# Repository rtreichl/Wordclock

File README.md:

# WortUhr

Wortuhr mit 12 × 12 Buchstaben, 500 × 500 mm. Frontplatte aus 1 mm Cortenstahl, die von Magneten gehalten wird. Lichtgitter aus 4 gedruckten Teilen. Vier gleiche LED-Platinen mit SK6812 RGBW; eine davon trägt als Master USB-C Power Delivery und den ESP32-S3 (ESPHome oder WLED). Aufbauhöhe 36 mm.

| Ordner | Inhalt |
|---|---|
| `00_Design/` | Grafik und Buchstabenlayout: Affinity-Datei, Pattern-SVGs, Frontplatten-DXF/-SVG (Schrift Sencilla) |
| `01_Mechanic/` | FreeCAD-Hauptmodell `FrontPlatte-Bestellung.FCStd` und Fertigungsdateien |
| `01_Mechanic/Frontplatte/` | Frontplatte 1 mm (STEP), DXF mit Lichtleiter-Bohrung zum Bestellen |
| `01_Mechanic/Gitter/` | Lichtgitter Q1–Q4 (STEP und druckfertige 3MF) |
| `01_Mechanic/Rueckrahmen/` | 8 Rückrahmen-Leisten (STEP) und 2 Druckplatten (3MF, je ≤ 254 × 254 mm) |
| `01_Mechanic/Diffusor/` | Diffusor 30 × 30 × 2 mm (DXF/STEP), 144 Stück |
| `02_Electronics/KiCad/` | KiCad-Projekt, Generator-Skripte (`tools/`), Projektbibliotheken und Platzhalter-3D-Modelle |
| `02_Electronics/BESTUECKUNG.md` | Bestückung, Kantenbrücken, Montage, WLED-Einstellungen |
| `02_Electronics/KiCad/ROUTING_GUIDE.md` | Regeln mit ID für Schaltplan, Layout, Routing und Review |
| `03_Software/ESPHome/` | Firmware für den ESP32-S3 (Uhrzeit per NTP, Home Assistant, Weboberfläche), siehe `README.md` dort |
| `03_Software/WLED/` | LED-Maps für WLED (1 oder 2 LEDs je Kammer) |
| `04_Rendering/` | Blender-Skript, Szene, Netze und Renderbilder |
| `05_Production/` | Geprüfte Fertigungsdaten je Bauteil mit Bericht `QUALIFIKATION.md`; Prüfskripte in `tools/` |
| `06_Datenblätter/` | Datenblätter, nur lokal (nicht eingecheckt) |
| `99_Archive/` | Ältere Modelle, Zwischenstände und erledigte Einmal-Skripte |

Ein Bild mit neuen Einstellungen rendern:

```
blender.exe -b -P 04_Rendering/render_wortuhr.py -- --samples 256 --res 2000x2000 --view angle
```

## Arbeiten am Projekt

Schaltplan und Platine entstehen aus `02_Electronics/KiCad/tools/design.py`. Jede Änderung wird gegen die Grenzen des Fertigers und gegen die Projektregeln geprüft; der GitHub-Workflow `production.yml` führt alle Prüfungen bei jedem Push aus. Regeln, Abläufe und Befehle stehen in `CLAUDE.md`, die Prüfskripte beschreibt `05_Production/tools/README.md`.

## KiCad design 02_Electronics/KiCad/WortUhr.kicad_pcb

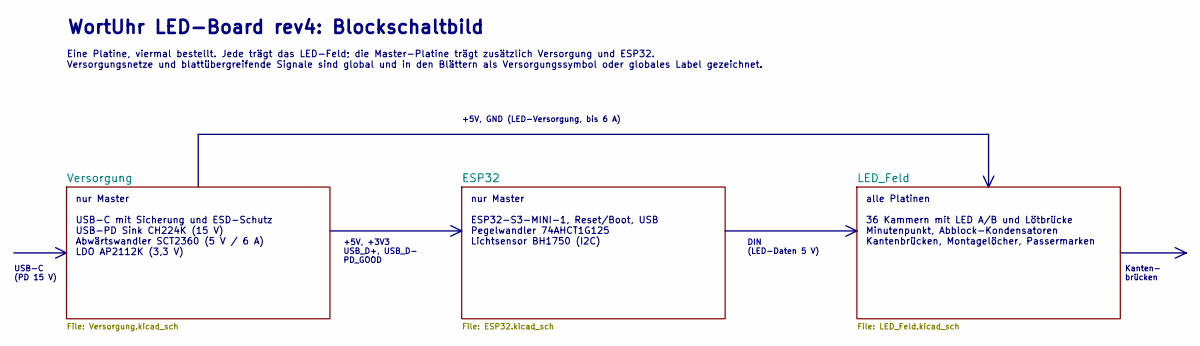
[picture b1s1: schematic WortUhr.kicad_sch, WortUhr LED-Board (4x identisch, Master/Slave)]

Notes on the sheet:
WortUhr LED-Board rev4: Blockschaltbild
Eine Platine, viermal bestellt. Jede trägt das LED-Feld; die Master-Platine trägt zusätzlich Versorgung und ESP32. Versorgungsnetze und blattübergreifende Signale sind global und in den Blättern als Versorgungssymbol oder globales Label gezeichnet.
nur Master USB-C mit Sicherung und ESD-Schutz USB-PD Sink CH224K (15 V) Abwärtswandler SCT2360 (5 V / 6 A) LDO AP2112K (3,3 V)
nur Master ESP32-S3-MINI-1, Reset/Boot, USB Pegelwandler 74AHCT1G125 Lichtsensor BH1750 (I2C)
alle Platinen 36 Kammern mit LED A/B und Lötbrücke Minutenpunkt, Abblock-Kondensatoren Kantenbrücken, Montagelöcher, Passermarken
+5V, +3V3 USB_D+, USB_D- PD_GOOD
DIN (LED-Daten 5 V)
+5V, GND (LED-Versorgung, bis 6 A)
USB-C (PD 15 V)
Kanten- brücken

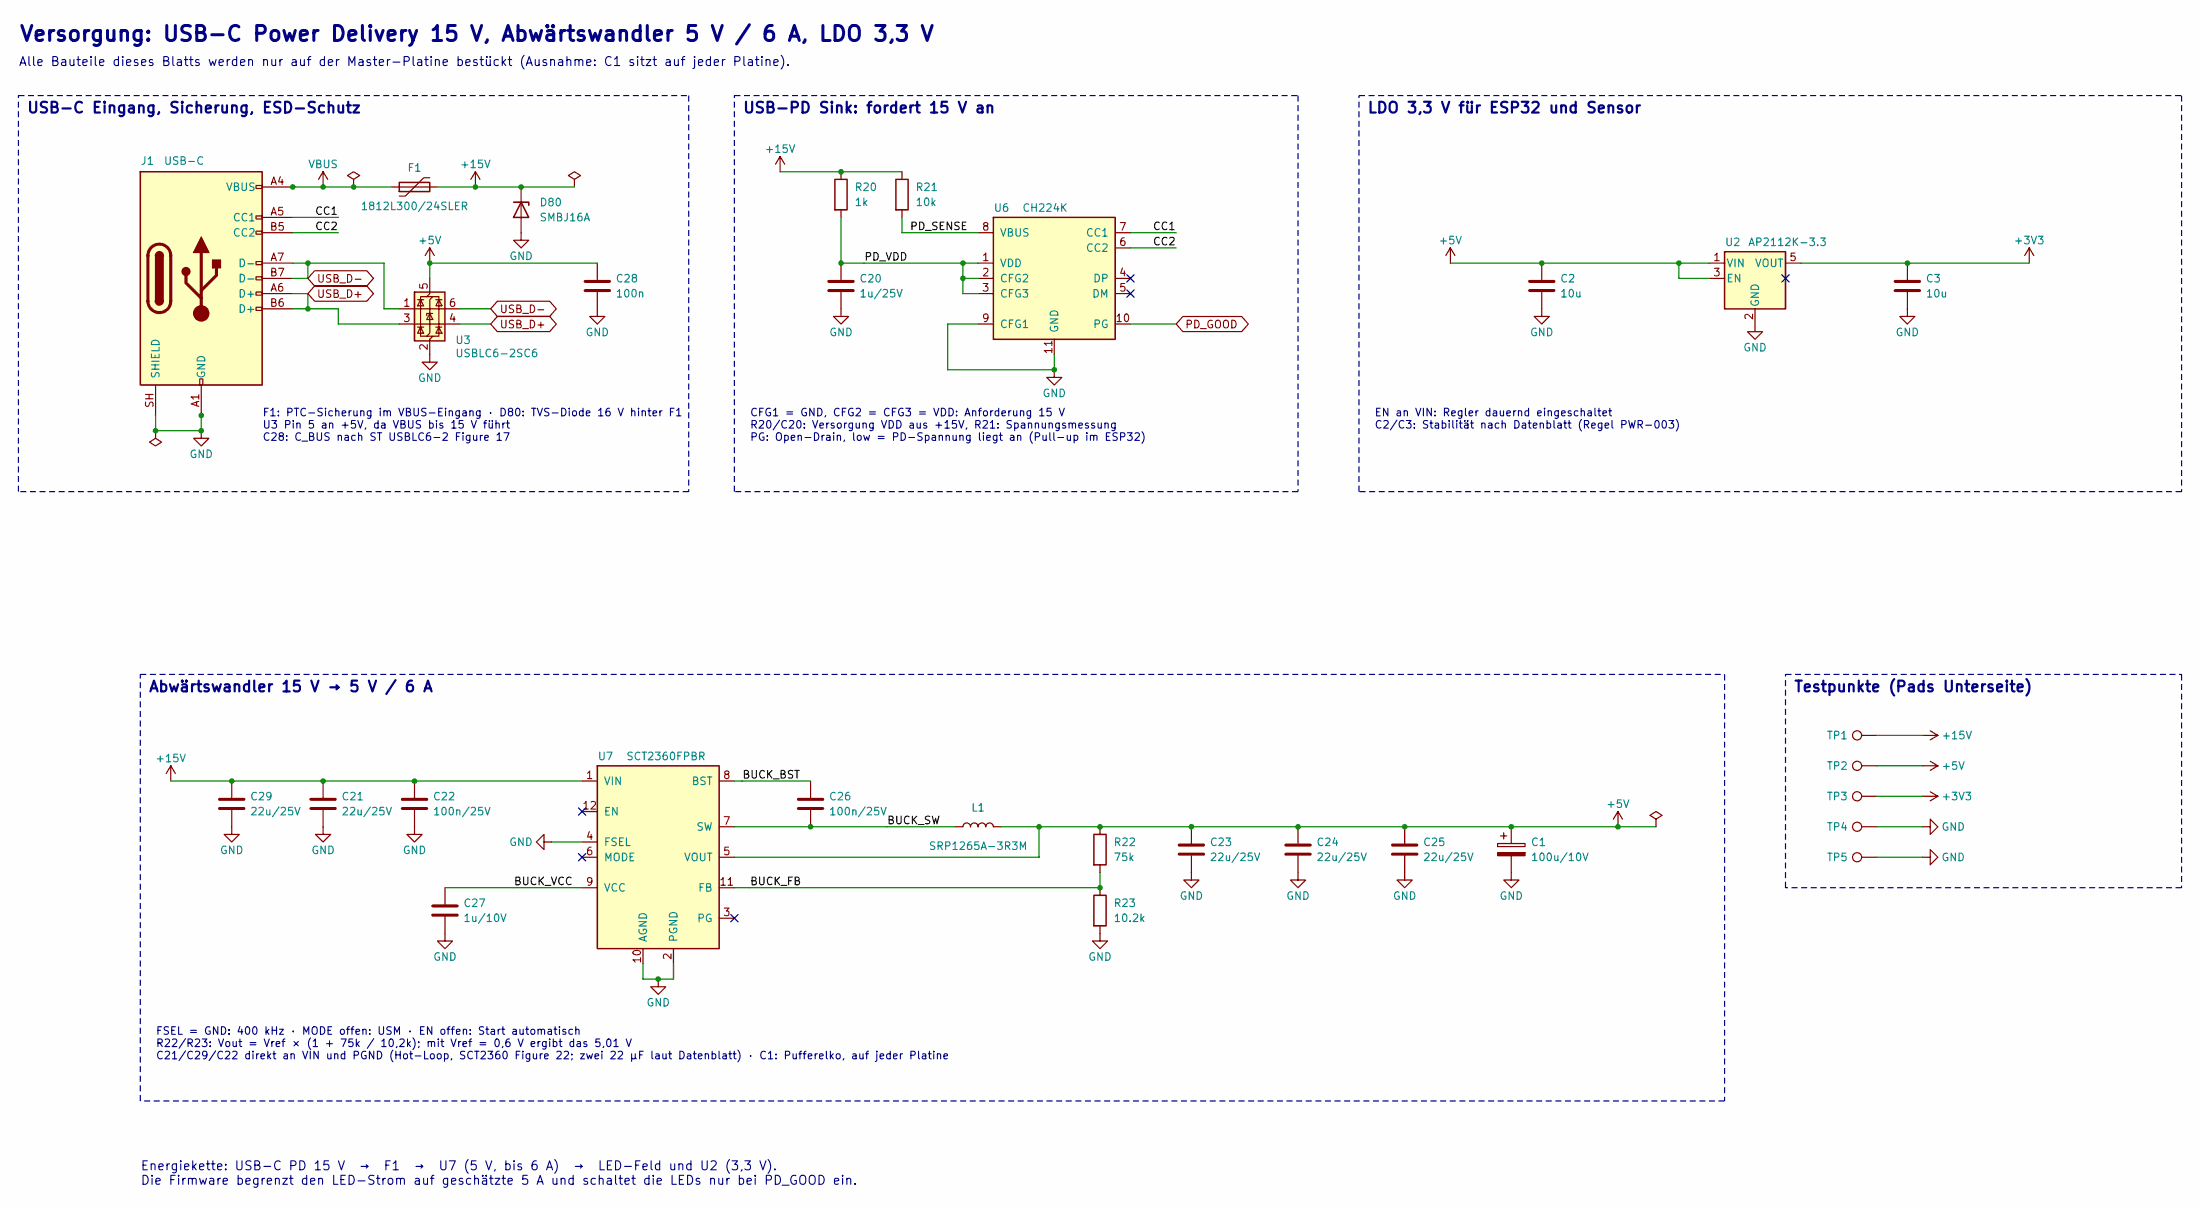
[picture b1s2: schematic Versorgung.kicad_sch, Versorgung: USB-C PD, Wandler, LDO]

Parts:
C1: 100u/10V; CP_Elec_6.3x7.7; MPN UWT1A101MCL1GB; DigiKey 493-2165-1-ND
C2, C3: 10u; C_0805_2012Metric; MPN TMK212BBJ106MG-T; DigiKey 587-6025-1-ND
C20: 1u/25V; C_0603_1608Metric; MPN C0603C105K3RACTU; DigiKey 399-C0603C105K3RACTUCT-ND
C21, C23, C24, C25, C29: 22u/25V; C_1206_3216Metric; MPN CC1206MKX5R8BB226; DigiKey 311-3522-1-ND
C22, C26: 100n/25V; C_0603_1608Metric; MPN C0603C104K5RACTU; DigiKey 399-C0603C104K5RACTUCT-ND
C27: 1u/10V; C_0603_1608Metric; MPN C0603C105K3RACTU; DigiKey 399-C0603C105K3RACTUCT-ND
C28: 100n; C_0603_1608Metric; MPN C0603C104K5RACTU; DigiKey 399-C0603C104K5RACTUCT-ND
D80: SMBJ16A; D_SMB; MPN SMBJ16A
F1: 1812L300/24SLER; Fuse_1812_4532Metric; MPN 1812L300/24SLER; DigiKey 18-1812L300/24SLERCT-ND
J1: USB-C; USB_C_Receptacle_HRO_TYPE-C-31-M-12; MPN TYPE-C-31-M-12
L1: SRP1265A-3R3M; L_Bourns_SRP1245A; MPN SRP1265A-3R3M; DigiKey SRP1265A-3R3MCT-ND
R20: 1k; R_1206_3216Metric; MPN RC1206FR-071KL; DigiKey 311-1.00KFRCT-ND
R21: 10k; R_0603_1608Metric; MPN ERJ-3EKF1002V; DigiKey P10.0KHCT-ND
R22: 75k; R_0603_1608Metric; MPN ERJ-3EKF7502V; DigiKey P75.0KHCT-ND
R23: 10.2k; R_0603_1608Metric; MPN ERJ-3EKF1022V; DigiKey P10.2KHCT-ND
TP1: +15V; TestPoint_Pad_D1.5mm
TP2: +5V; TestPoint_Pad_D1.5mm
TP3: +3V3; TestPoint_Pad_D1.5mm
TP4, TP5: GND; TestPoint_Pad_D1.5mm
U2: AP2112K-3.3; SOT-23-5; MPN AP2112K-3.3TRG1; DigiKey AP2112K-3.3TRG1DICT-ND
U3: USBLC6-2SC6; SOT-23-6; MPN USBLC6-2SC6; DigiKey 497-5235-1-ND
U6: CH224K; SSOP-10-1EP_3.9x4.9mm_P1mm_EP2.1x3.3mm; MPN CH224K
U7: SCT2360FPBR; QFN-12_SCT2360; MPN SCT2360FPBR

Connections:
+3V3: C3.1, TP3.1, U2.5 (VOUT); also elsewhere on the board
+5V: C1.1, C2.1, C23.1, C24.1, C25.1, C28.1, L1.2, R22.1, TP2.1, U2.1 (VIN), U2.3 (EN), U3.5 (VBUS), U7.5 (VOUT); also elsewhere on the board
+15V: C21.1, C22.1, C29.1, D80.1 (K), F1.2, R20.1, R21.1, TP1.1, U7.1 (VIN)
/Versorgung/BUCK_BST: C26.1, U7.8 (BST)
/Versorgung/BUCK_FB: R22.2, R23.1, U7.11 (FB)
/Versorgung/BUCK_SW: C26.2, L1.1, U7.7 (SW)
/Versorgung/BUCK_VCC: C27.1, U7.9 (VCC)
/Versorgung/CC1: J1.A5 (CC1), U6.7 (CC1)
/Versorgung/CC2: J1.B5 (CC2), U6.6 (CC2)
/Versorgung/PD_SENSE: R21.2, U6.8 (VBUS)
/Versorgung/PD_VDD: C20.1, R20.2, U6.1 (VDD), U6.2 (CFG2), U6.3 (CFG3)
GND: C1.2, C2.2, C3.2, C20.2, C21.2, C22.2, C23.2, C24.2, C25.2, C27.2, C28.2, C29.2, D80.2 (A), J1.A1 (GND), J1.A12 (GND), J1.B1 (GND), J1.B12 (GND), J1.SH (SHIELD), R23.2, TP4.1, TP5.1, U2.2 (GND), U3.2 (GND), U6.9 (CFG1), U6.11 (GND), U7.2 (PGND), U7.4 (FSEL), U7.10 (AGND); also elsewhere on the board
PD_GOOD: U6.10 (PG); also elsewhere on the board
USB_D+: J1.A6 (D+), J1.B6 (D+), U3.3 (I/O2), U3.4 (I/O2); also elsewhere on the board
USB_D-: J1.A7 (D-), J1.B7 (D-), U3.1 (I/O1), U3.6 (I/O1); also elsewhere on the board
VBUS: F1.1, J1.A4 (VBUS), J1.A9 (VBUS), J1.B4 (VBUS), J1.B9 (VBUS)

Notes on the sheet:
Versorgung: USB-C Power Delivery 15 V, Abwärtswandler 5 V / 6 A, LDO 3,3 V
Alle Bauteile dieses Blatts werden nur auf der Master-Platine bestückt (Ausnahme: C1 sitzt auf jeder Platine).
USB-C Eingang, Sicherung, ESD-Schutz
F1: PTC-Sicherung im VBUS-Eingang · D80: TVS-Diode 16 V hinter F1 U3 Pin 5 an +5V, da VBUS bis 15 V führt C28: C_BUS nach ST USBLC6-2 Figure 17
USB-PD Sink: fordert 15 V an
CFG1 = GND, CFG2 = CFG3 = VDD: Anforderung 15 V R20/C20: Versorgung VDD aus +15V, R21: Spannungsmessung PG: Open-Drain, low = PD-Spannung liegt an (Pull-up im ESP32)
LDO 3,3 V für ESP32 und Sensor
EN an VIN: Regler dauernd eingeschaltet C2/C3: Stabilität nach Datenblatt (Regel PWR-003)
Abwärtswandler 15 V → 5 V / 6 A
FSEL = GND: 400 kHz · MODE offen: USM · EN offen: Start automatisch R22/R23: Vout = Vref × (1 + 75k / 10,2k); mit Vref = 0,6 V ergibt das 5,01 V C21/C29/C22 direkt an VIN und PGND (Hot-Loop, SCT2360 Figure 22; zwei 22 µF laut Datenblatt) · C1: Pufferelko, auf jeder Platine
Testpunkte (Pads Unterseite)
Energiekette: USB-C PD 15 V → F1 → U7 (5 V, bis 6 A) → LED-Feld und U2 (3,3 V). Die Firmware begrenzt den LED-Strom auf geschätzte 5 A und schaltet die LEDs nur bei PD_GOOD ein.

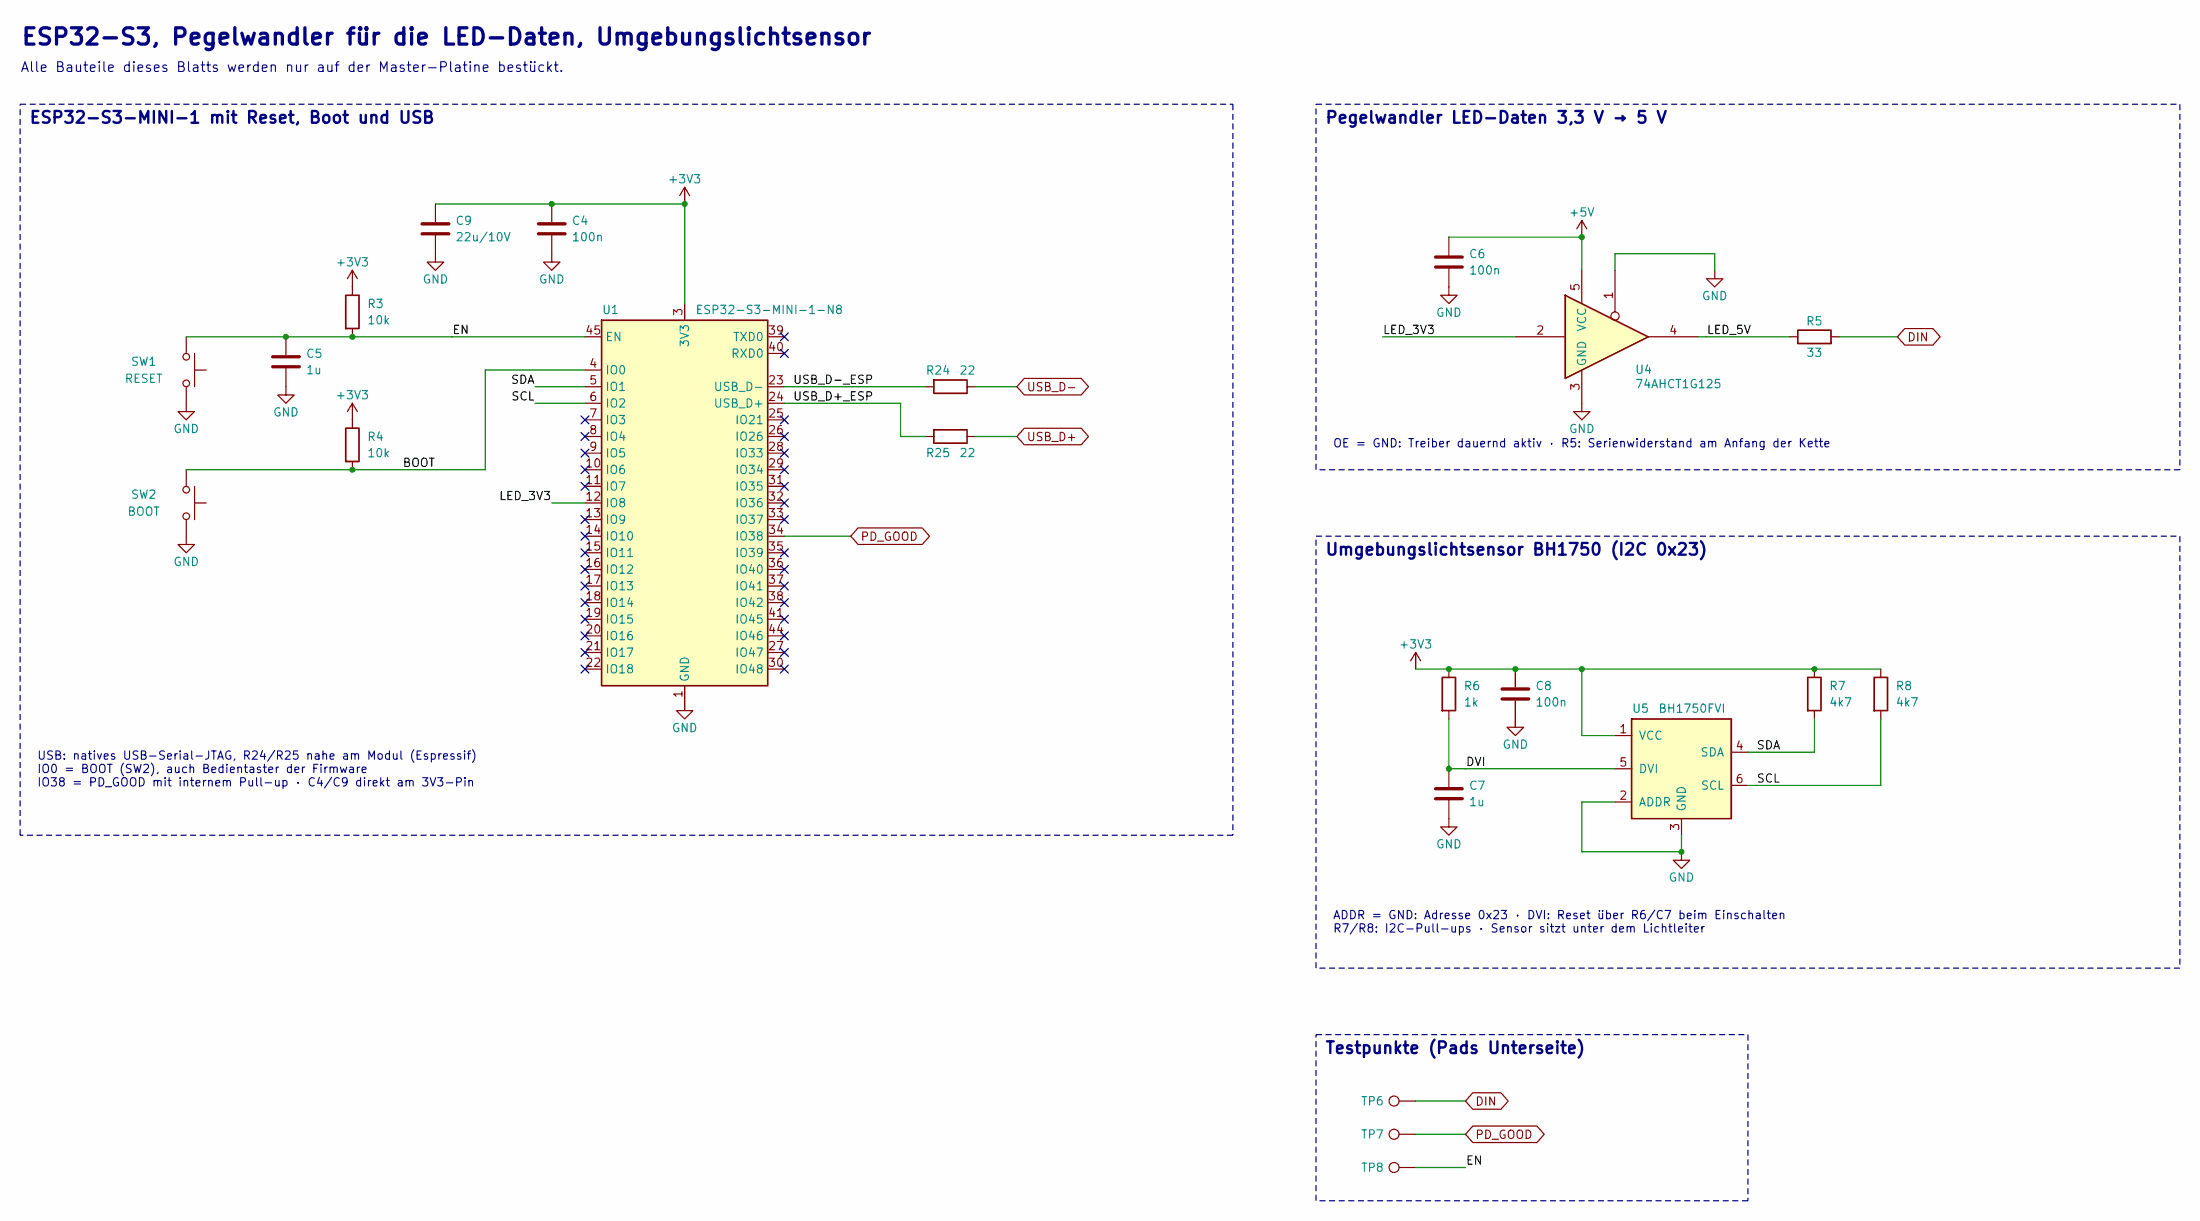
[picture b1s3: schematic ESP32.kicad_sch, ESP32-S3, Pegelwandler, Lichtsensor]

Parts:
C4, C6, C8: 100n; C_0603_1608Metric; MPN C0603C104K5RACTU; DigiKey 399-C0603C104K5RACTUCT-ND
C5, C7: 1u; C_0603_1608Metric; MPN C0603C105K3RACTU; DigiKey 399-C0603C105K3RACTUCT-ND
C9: 22u/10V; C_0805_2012Metric; MPN C0805C226M8PACTU; DigiKey 399-C0805C226M8PACTUCT-ND
R3, R4: 10k; R_0603_1608Metric; MPN ERJ-3EKF1002V; DigiKey P10.0KHCT-ND
R5: 33; R_0603_1608Metric; MPN ERJ-3EKF33R0V; DigiKey P33.0HCT-ND
R6: 1k; R_0603_1608Metric; MPN ERJ-3EKF1001V; DigiKey P1.00KHCT-ND
R7, R8: 4k7; R_0603_1608Metric; MPN ERJ-3EKF4701V; DigiKey P4.70KHCT-ND
R24, R25: 22; R_0402_1005Metric; MPN ERJ-2RKF22R0X; DigiKey P22.0LCT-ND
SW1: RESET; SW_SPST_TL3342; MPN TL3342F160QG/TR; DigiKey EG2531CT-ND
SW2: BOOT; SW_SPST_TL3342; MPN TL3342F160QG/TR; DigiKey EG2531CT-ND
TP6: DIN; TestPoint_Pad_D1.5mm
TP7: PD_GOOD; TestPoint_Pad_D1.5mm
TP8: EN; TestPoint_Pad_D1.5mm
U1: ESP32-S3-MINI-1-N8; ESP32-S2-MINI-1; MPN ESP32-S3-MINI-1-N8; DigiKey 5407-ESP32-S3-MINI-1-N8CT-ND
U4: 74AHCT1G125; SOT-23-5; MPN SN74AHCT1G125DBVR; DigiKey 296-4708-1-ND
U5: BH1750FVI; WSOF6I_BH1750; MPN BH1750FVI-TR; DigiKey BH1750FVICT-ND

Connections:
+3V3: C4.1, C8.1, C9.1, R3.1, R4.1, R6.1, R7.1, R8.1, U1.3 (3V3), U5.1 (VCC); also elsewhere on the board
+5V: C6.1, U4.5 (VCC); also elsewhere on the board
/ESP32/BOOT: R4.2, SW2.1, U1.4 (IO0)
/ESP32/DVI: C7.1, R6.2, U5.5 (DVI)
/ESP32/EN: C5.1, R3.2, SW1.1, TP8.1, U1.45 (EN)
/ESP32/LED_3V3: U1.12 (IO8), U4.2
/ESP32/LED_5V: R5.1, U4.4
/ESP32/SCL: R8.2, U1.6 (IO2), U5.6 (SCL)
/ESP32/SDA: R7.2, U1.5 (IO1), U5.4 (SDA)
/ESP32/USB_D+_ESP: R25.2, U1.24 (USB_D+)
/ESP32/USB_D-_ESP: R24.2, U1.23 (USB_D-)
DIN: R5.2, TP6.1; also elsewhere on the board
GND: C4.2, C5.2, C6.2, C7.2, C8.2, C9.2, SW1.2, SW2.2, U1.1 (GND), U1.2 (GND), U1.42 (GND), U1.43 (GND), U1.46 (GND), U1.47 (GND), U1.48 (GND), U1.49 (GND), U1.50 (GND), U1.51 (GND), U1.52 (GND), U1.53 (GND), U1.54 (GND), U1.55 (GND), U1.56 (GND), U1.57 (GND), U1.58 (GND), U1.59 (GND), U1.60 (GND), U1.61 (GND), U1.62 (GND), U1.63 (GND), U1.64 (GND), U1.65 (GND), U4.1, U4.3 (GND), U5.2 (ADDR), U5.3 (GND); also elsewhere on the board
PD_GOOD: TP7.1, U1.34 (IO38); also elsewhere on the board
USB_D+: R25.1; also elsewhere on the board
USB_D-: R24.1; also elsewhere on the board

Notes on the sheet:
ESP32-S3, Pegelwandler für die LED-Daten, Umgebungslichtsensor
Alle Bauteile dieses Blatts werden nur auf der Master-Platine bestückt.
ESP32-S3-MINI-1 mit Reset, Boot und USB
USB: natives USB-Serial-JTAG, R24/R25 nahe am Modul (Espressif) IO0 = BOOT (SW2), auch Bedientaster der Firmware IO38 = PD_GOOD mit internem Pull-up · C4/C9 direkt am 3V3-Pin
Pegelwandler LED-Daten 3,3 V → 5 V
OE = GND: Treiber dauernd aktiv · R5: Serienwiderstand am Anfang der Kette
Umgebungslichtsensor BH1750 (I2C 0x23)
ADDR = GND: Adresse 0x23 · DVI: Reset über R6/C7 beim Einschalten R7/R8: I2C-Pull-ups · Sensor sitzt unter dem Lichtleiter
Testpunkte (Pads Unterseite)

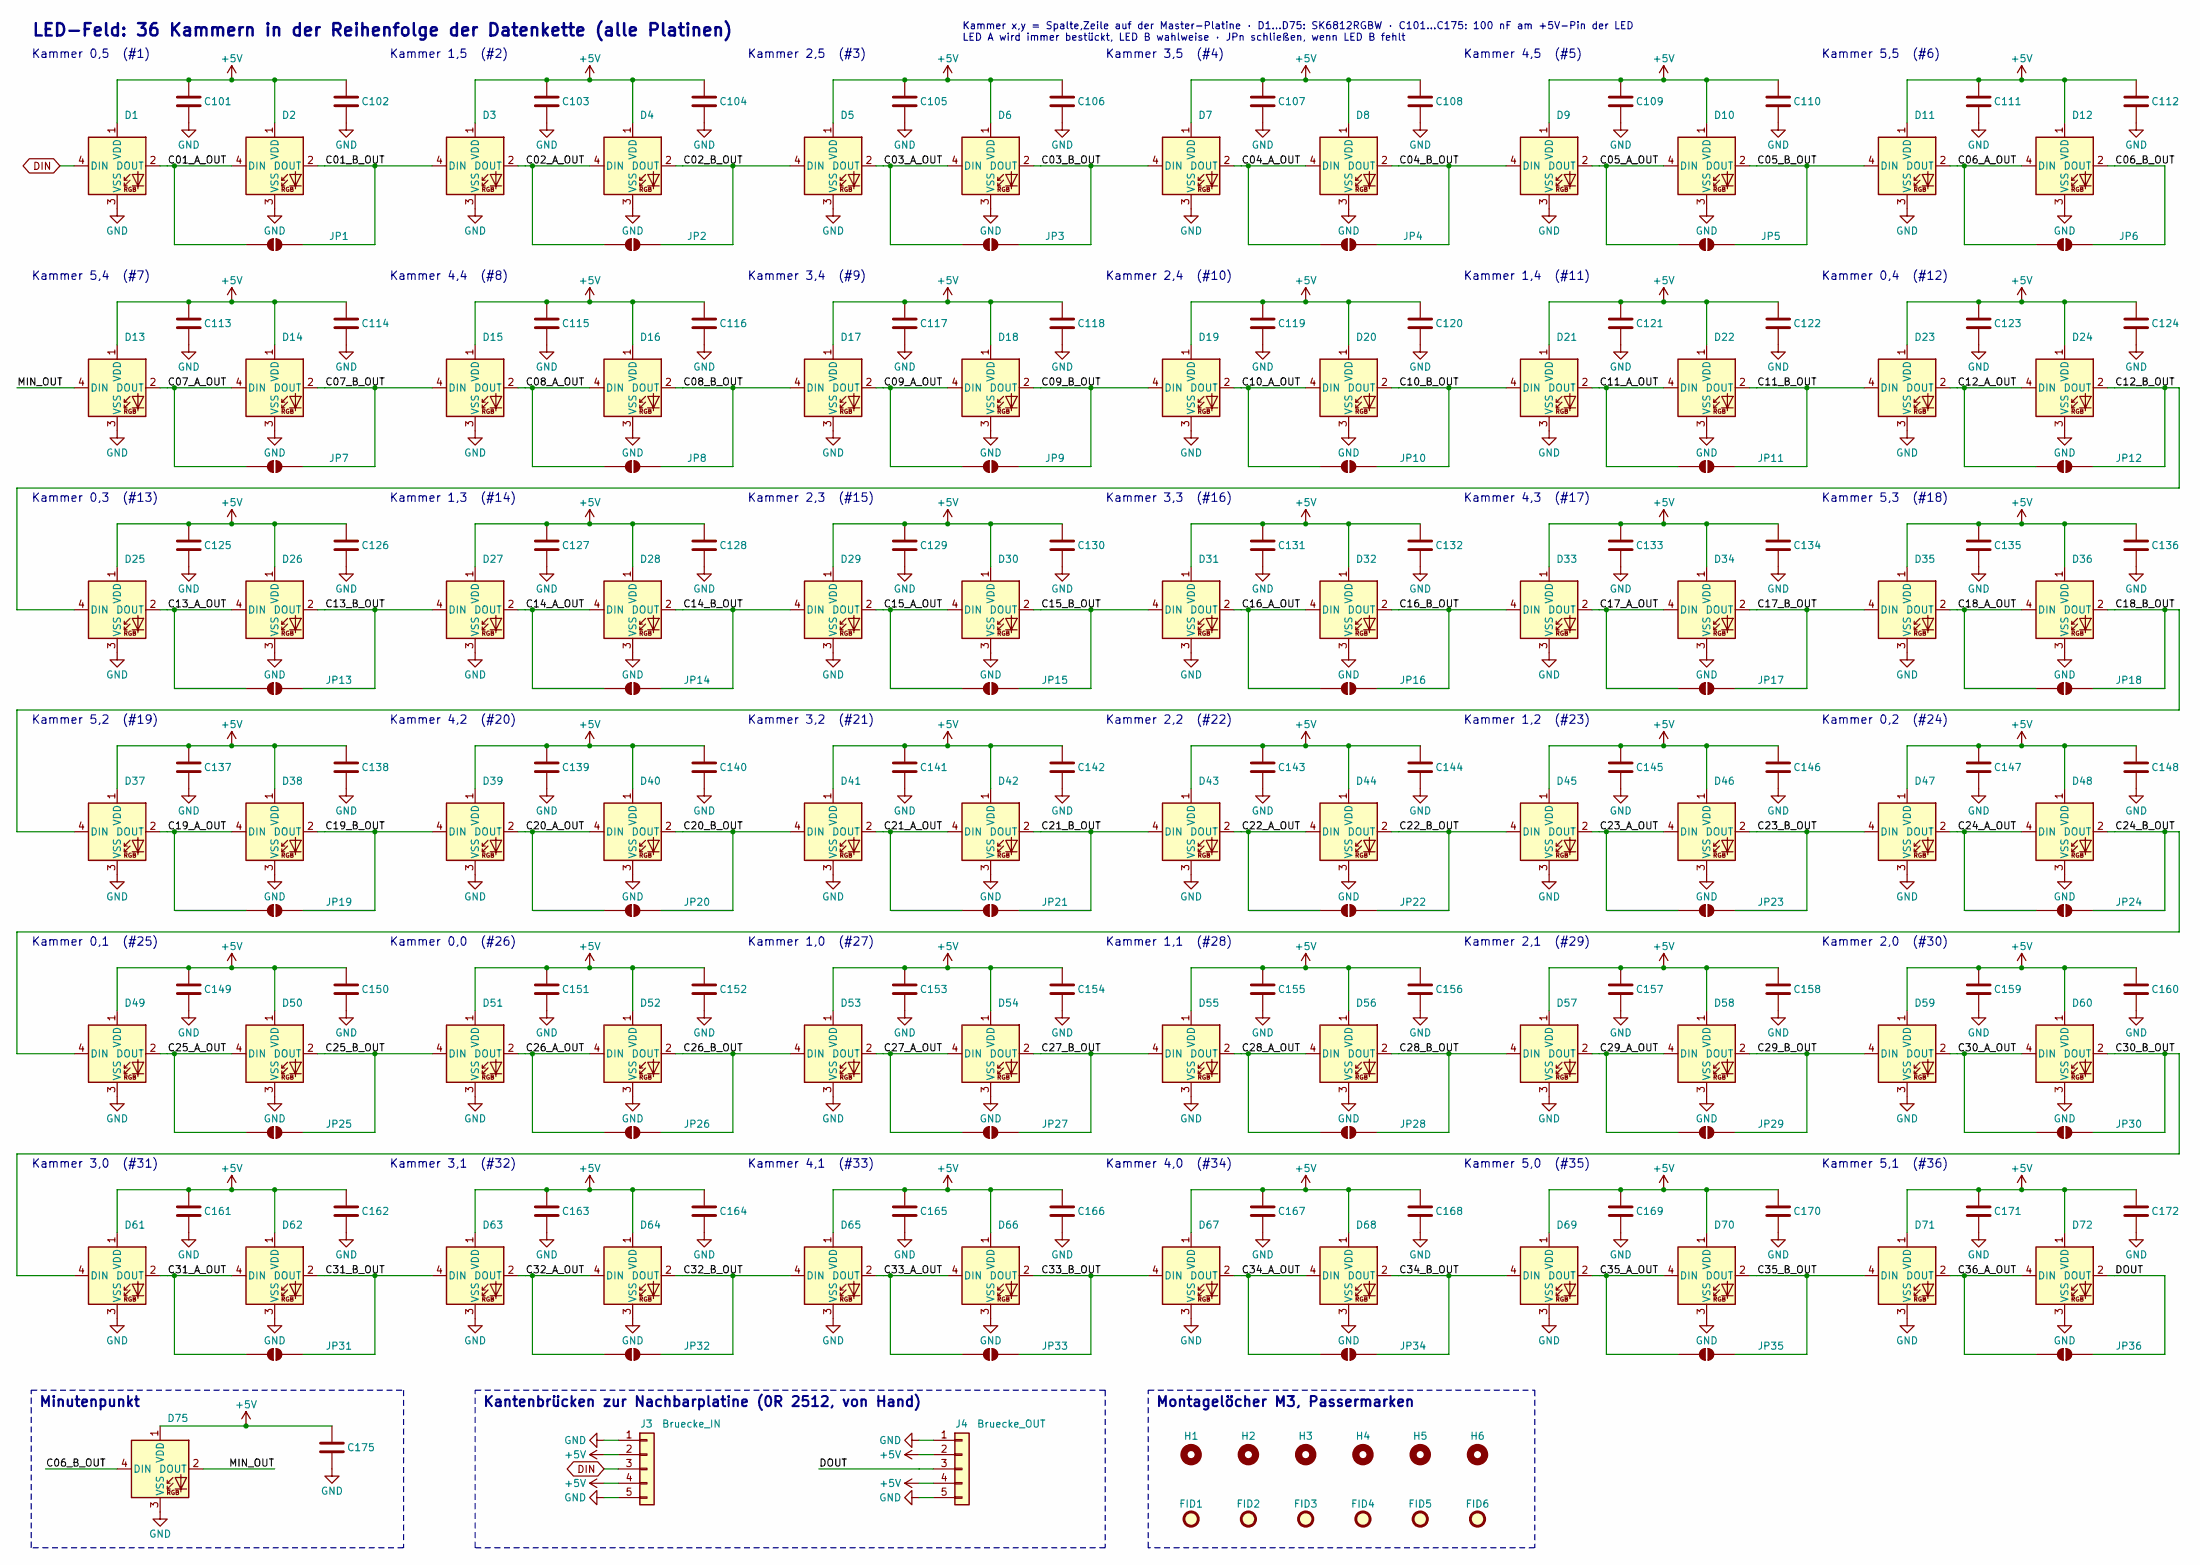
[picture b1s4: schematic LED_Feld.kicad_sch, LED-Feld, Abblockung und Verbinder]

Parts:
C101, C102, C103, C104, C105, C106, C107, C108, C109, C110, C111, C112, C113, C114, C115, C116, C117, C118, C119, C120, C121, C122, C123, C124, C125, C126, C127, C128, C129, C130, C131, C132, C133, C134, C135, C136, C137, C138, C139, C140, C141, C142, C143, C144, C145, C146, C147, C148, C149, C150, C151, C152, C153, C154, C155, C156, C157, C158, C159, C160, C161, C162, C163, C164, C165, C166, C167, C168, C169, C170, C171, C172, C175: 100n; C_0603_1608Metric; MPN C0603C104K5RACTU; DigiKey 399-C0603C104K5RACTUCT-ND
D1, D2, D3, D4, D5, D6, D7, D8, D9, D10, D11, D12, D13, D14, D15, D16, D17, D18, D19, D20, D21, D22, D23, D24, D25, D26, D27, D28, D29, D30, D31, D32, D33, D34, D35, D36, D37, D38, D39, D40, D41, D42, D43, D44, D45, D46, D47, D48, D49, D50, D51, D52, D53, D54, D55, D56, D57, D58, D59, D60, D61, D62, D63, D64, D65, D66, D67, D68, D69, D70, D71, D72, D75: SK6812RGBW; LED_WS2812B_PLCC4_5.0x5.0mm_P3.2mm
FID1, FID2, FID3, FID4, FID5, FID6: Fiducial; Fiducial_1mm_Mask2mm
H1, H2, H3, H4, H5, H6: M3; MountingHole_4.3mm_M4
J3: Bruecke_IN; EdgeBridge_5x2512
J4: Bruecke_OUT; EdgeBridge_5x2512
JP1, JP2, JP3, JP4, JP5, JP6, JP7, JP8, JP9, JP10, JP11, JP12, JP13, JP14, JP15, JP16, JP17, JP18, JP19, JP20, JP21, JP22, JP23, JP24, JP25, JP26, JP27, JP28, JP29, JP30, JP31, JP32, JP33, JP34, JP35, JP36: Bruecke LED B; SolderJumper-2_P1.3mm_Open_RoundedPad1.0x1.5mm

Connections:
+5V: C101.2, C102.2, C103.2, C104.2, C105.2, C106.2, C107.2, C108.2, C109.2, C110.2, C111.2, C112.2, C113.2, C114.2, C115.2, C116.2, C117.2, C118.2, C119.2, C120.2, C121.2, C122.2, C123.2, C124.2, C125.2, C126.2, C127.2, C128.2, C129.2, C130.2, C131.2, C132.2, C133.2, C134.2, C135.2, C136.2, C137.2, C138.2, C139.2, C140.2, C141.2, C142.2, C143.2, C144.2, C145.2, C146.2, C147.2, C148.2, C149.2, C150.2, C151.2, C152.2, C153.2, C154.2, C155.2, C156.2, C157.2, C158.2, C159.2, C160.2, C161.2, C162.2, C163.2, C164.2, C165.2, C166.2, C167.2, C168.2, C169.2, C170.2, C171.2, C172.2, C175.2, D1.1 (VDD), D2.1 (VDD), D3.1 (VDD), D4.1 (VDD), D5.1 (VDD), D6.1 (VDD), D7.1 (VDD), D8.1 (VDD), D9.1 (VDD), D10.1 (VDD), D11.1 (VDD), D12.1 (VDD), D13.1 (VDD), D14.1 (VDD), D15.1 (VDD), D16.1 (VDD), D17.1 (VDD), D18.1 (VDD), D19.1 (VDD), D20.1 (VDD), D21.1 (VDD), D22.1 (VDD), D23.1 (VDD), D24.1 (VDD), D25.1 (VDD), D26.1 (VDD), D27.1 (VDD), D28.1 (VDD), D29.1 (VDD), D30.1 (VDD), D31.1 (VDD), D32.1 (VDD), D33.1 (VDD), D34.1 (VDD), D35.1 (VDD), D36.1 (VDD), D37.1 (VDD), D38.1 (VDD), D39.1 (VDD), D40.1 (VDD), D41.1 (VDD), D42.1 (VDD), D43.1 (VDD), D44.1 (VDD), D45.1 (VDD), D46.1 (VDD), D47.1 (VDD), D48.1 (VDD), D49.1 (VDD), D50.1 (VDD), D51.1 (VDD), D52.1 (VDD), D53.1 (VDD), D54.1 (VDD), D55.1 (VDD), D56.1 (VDD), D57.1 (VDD), D58.1 (VDD), D59.1 (VDD), D60.1 (VDD), D61.1 (VDD), D62.1 (VDD), D63.1 (VDD), D64.1 (VDD), D65.1 (VDD), D66.1 (VDD), D67.1 (VDD), D68.1 (VDD), D69.1 (VDD), D70.1 (VDD), D71.1 (VDD), D72.1 (VDD), D75.1 (VDD), J3.2, J3.4, J4.2, J4.4; also elsewhere on the board
/LED_Feld/DOUT: D72.2 (DOUT), J4.3, JP36.2 (B)
/LED_Feld/K01_A_OUT: D1.2 (DOUT), D2.4 (DIN), JP1.1 (A)
/LED_Feld/K01_B_OUT: D2.2 (DOUT), D3.4 (DIN), JP1.2 (B)
/LED_Feld/K02_A_OUT: D3.2 (DOUT), D4.4 (DIN), JP2.1 (A)
/LED_Feld/K02_B_OUT: D4.2 (DOUT), D5.4 (DIN), JP2.2 (B)
/LED_Feld/K03_A_OUT: D5.2 (DOUT), D6.4 (DIN), JP3.1 (A)
/LED_Feld/K03_B_OUT: D6.2 (DOUT), D7.4 (DIN), JP3.2 (B)
/LED_Feld/K04_A_OUT: D7.2 (DOUT), D8.4 (DIN), JP4.1 (A)
/LED_Feld/K04_B_OUT: D8.2 (DOUT), D9.4 (DIN), JP4.2 (B)
/LED_Feld/K05_A_OUT: D9.2 (DOUT), D10.4 (DIN), JP5.1 (A)
/LED_Feld/K05_B_OUT: D10.2 (DOUT), D11.4 (DIN), JP5.2 (B)
/LED_Feld/K06_A_OUT: D11.2 (DOUT), D12.4 (DIN), JP6.1 (A)
/LED_Feld/K06_B_OUT: D12.2 (DOUT), D75.4 (DIN), JP6.2 (B)
/LED_Feld/K07_A_OUT: D13.2 (DOUT), D14.4 (DIN), JP7.1 (A)
/LED_Feld/K07_B_OUT: D14.2 (DOUT), D15.4 (DIN), JP7.2 (B)
/LED_Feld/K08_A_OUT: D15.2 (DOUT), D16.4 (DIN), JP8.1 (A)
/LED_Feld/K08_B_OUT: D16.2 (DOUT), D17.4 (DIN), JP8.2 (B)
/LED_Feld/K09_A_OUT: D17.2 (DOUT), D18.4 (DIN), JP9.1 (A)
/LED_Feld/K09_B_OUT: D18.2 (DOUT), D19.4 (DIN), JP9.2 (B)
/LED_Feld/K10_A_OUT: D19.2 (DOUT), D20.4 (DIN), JP10.1 (A)
/LED_Feld/K10_B_OUT: D20.2 (DOUT), D21.4 (DIN), JP10.2 (B)
/LED_Feld/K11_A_OUT: D21.2 (DOUT), D22.4 (DIN), JP11.1 (A)
/LED_Feld/K11_B_OUT: D22.2 (DOUT), D23.4 (DIN), JP11.2 (B)
/LED_Feld/K12_A_OUT: D23.2 (DOUT), D24.4 (DIN), JP12.1 (A)
/LED_Feld/K12_B_OUT: D24.2 (DOUT), D25.4 (DIN), JP12.2 (B)
/LED_Feld/K13_A_OUT: D25.2 (DOUT), D26.4 (DIN), JP13.1 (A)
/LED_Feld/K13_B_OUT: D26.2 (DOUT), D27.4 (DIN), JP13.2 (B)
/LED_Feld/K14_A_OUT: D27.2 (DOUT), D28.4 (DIN), JP14.1 (A)
/LED_Feld/K14_B_OUT: D28.2 (DOUT), D29.4 (DIN), JP14.2 (B)
/LED_Feld/K15_A_OUT: D29.2 (DOUT), D30.4 (DIN), JP15.1 (A)
/LED_Feld/K15_B_OUT: D30.2 (DOUT), D31.4 (DIN), JP15.2 (B)
/LED_Feld/K16_A_OUT: D31.2 (DOUT), D32.4 (DIN), JP16.1 (A)
/LED_Feld/K16_B_OUT: D32.2 (DOUT), D33.4 (DIN), JP16.2 (B)
/LED_Feld/K17_A_OUT: D33.2 (DOUT), D34.4 (DIN), JP17.1 (A)
/LED_Feld/K17_B_OUT: D34.2 (DOUT), D35.4 (DIN), JP17.2 (B)
/LED_Feld/K18_A_OUT: D35.2 (DOUT), D36.4 (DIN), JP18.1 (A)
/LED_Feld/K18_B_OUT: D36.2 (DOUT), D37.4 (DIN), JP18.2 (B)
/LED_Feld/K19_A_OUT: D37.2 (DOUT), D38.4 (DIN), JP19.1 (A)
/LED_Feld/K19_B_OUT: D38.2 (DOUT), D39.4 (DIN), JP19.2 (B)
/LED_Feld/K20_A_OUT: D39.2 (DOUT), D40.4 (DIN), JP20.1 (A)
/LED_Feld/K20_B_OUT: D40.2 (DOUT), D41.4 (DIN), JP20.2 (B)
/LED_Feld/K21_A_OUT: D41.2 (DOUT), D42.4 (DIN), JP21.1 (A)
/LED_Feld/K21_B_OUT: D42.2 (DOUT), D43.4 (DIN), JP21.2 (B)
/LED_Feld/K22_A_OUT: D43.2 (DOUT), D44.4 (DIN), JP22.1 (A)
/LED_Feld/K22_B_OUT: D44.2 (DOUT), D45.4 (DIN), JP22.2 (B)
/LED_Feld/K23_A_OUT: D45.2 (DOUT), D46.4 (DIN), JP23.1 (A)
/LED_Feld/K23_B_OUT: D46.2 (DOUT), D47.4 (DIN), JP23.2 (B)
/LED_Feld/K24_A_OUT: D47.2 (DOUT), D48.4 (DIN), JP24.1 (A)
/LED_Feld/K24_B_OUT: D48.2 (DOUT), D49.4 (DIN), JP24.2 (B)
/LED_Feld/K25_A_OUT: D49.2 (DOUT), D50.4 (DIN), JP25.1 (A)
/LED_Feld/K25_B_OUT: D50.2 (DOUT), D51.4 (DIN), JP25.2 (B)
/LED_Feld/K26_A_OUT: D51.2 (DOUT), D52.4 (DIN), JP26.1 (A)
/LED_Feld/K26_B_OUT: D52.2 (DOUT), D53.4 (DIN), JP26.2 (B)
/LED_Feld/K27_A_OUT: D53.2 (DOUT), D54.4 (DIN), JP27.1 (A)
/LED_Feld/K27_B_OUT: D54.2 (DOUT), D55.4 (DIN), JP27.2 (B)
/LED_Feld/K28_A_OUT: D55.2 (DOUT), D56.4 (DIN), JP28.1 (A)
/LED_Feld/K28_B_OUT: D56.2 (DOUT), D57.4 (DIN), JP28.2 (B)
/LED_Feld/K29_A_OUT: D57.2 (DOUT), D58.4 (DIN), JP29.1 (A)
/LED_Feld/K29_B_OUT: D58.2 (DOUT), D59.4 (DIN), JP29.2 (B)
/LED_Feld/K30_A_OUT: D59.2 (DOUT), D60.4 (DIN), JP30.1 (A)
/LED_Feld/K30_B_OUT: D60.2 (DOUT), D61.4 (DIN), JP30.2 (B)
/LED_Feld/K31_A_OUT: D61.2 (DOUT), D62.4 (DIN), JP31.1 (A)
/LED_Feld/K31_B_OUT: D62.2 (DOUT), D63.4 (DIN), JP31.2 (B)
/LED_Feld/K32_A_OUT: D63.2 (DOUT), D64.4 (DIN), JP32.1 (A)
/LED_Feld/K32_B_OUT: D64.2 (DOUT), D65.4 (DIN), JP32.2 (B)
/LED_Feld/K33_A_OUT: D65.2 (DOUT), D66.4 (DIN), JP33.1 (A)
/LED_Feld/K33_B_OUT: D66.2 (DOUT), D67.4 (DIN), JP33.2 (B)
/LED_Feld/K34_A_OUT: D67.2 (DOUT), D68.4 (DIN), JP34.1 (A)
/LED_Feld/K34_B_OUT: D68.2 (DOUT), D69.4 (DIN), JP34.2 (B)
/LED_Feld/K35_A_OUT: D69.2 (DOUT), D70.4 (DIN), JP35.1 (A)
/LED_Feld/K35_B_OUT: D70.2 (DOUT), D71.4 (DIN), JP35.2 (B)
/LED_Feld/K36_A_OUT: D71.2 (DOUT), D72.4 (DIN), JP36.1 (A)
/LED_Feld/MIN_OUT: D13.4 (DIN), D75.2 (DOUT)
DIN: D1.4 (DIN), J3.3; also elsewhere on the board
GND: C101.1, C102.1, C103.1, C104.1, C105.1, C106.1, C107.1, C108.1, C109.1, C110.1, C111.1, C112.1, C113.1, C114.1, C115.1, C116.1, C117.1, C118.1, C119.1, C120.1, C121.1, C122.1, C123.1, C124.1, C125.1, C126.1, C127.1, C128.1, C129.1, C130.1, C131.1, C132.1, C133.1, C134.1, C135.1, C136.1, C137.1, C138.1, C139.1, C140.1, C141.1, C142.1, C143.1, C144.1, C145.1, C146.1, C147.1, C148.1, C149.1, C150.1, C151.1, C152.1, C153.1, C154.1, C155.1, C156.1, C157.1, C158.1, C159.1, C160.1, C161.1, C162.1, C163.1, C164.1, C165.1, C166.1, C167.1, C168.1, C169.1, C170.1, C171.1, C172.1, C175.1, D1.3 (VSS), D2.3 (VSS), D3.3 (VSS), D4.3 (VSS), D5.3 (VSS), D6.3 (VSS), D7.3 (VSS), D8.3 (VSS), D9.3 (VSS), D10.3 (VSS), D11.3 (VSS), D12.3 (VSS), D13.3 (VSS), D14.3 (VSS), D15.3 (VSS), D16.3 (VSS), D17.3 (VSS), D18.3 (VSS), D19.3 (VSS), D20.3 (VSS), D21.3 (VSS), D22.3 (VSS), D23.3 (VSS), D24.3 (VSS), D25.3 (VSS), D26.3 (VSS), D27.3 (VSS), D28.3 (VSS), D29.3 (VSS), D30.3 (VSS), D31.3 (VSS), D32.3 (VSS), D33.3 (VSS), D34.3 (VSS), D35.3 (VSS), D36.3 (VSS), D37.3 (VSS), D38.3 (VSS), D39.3 (VSS), D40.3 (VSS), D41.3 (VSS), D42.3 (VSS), D43.3 (VSS), D44.3 (VSS), D45.3 (VSS), D46.3 (VSS), D47.3 (VSS), D48.3 (VSS), D49.3 (VSS), D50.3 (VSS), D51.3 (VSS), D52.3 (VSS), D53.3 (VSS), D54.3 (VSS), D55.3 (VSS), D56.3 (VSS), D57.3 (VSS), D58.3 (VSS), D59.3 (VSS), D60.3 (VSS), D61.3 (VSS), D62.3 (VSS), D63.3 (VSS), D64.3 (VSS), D65.3 (VSS), D66.3 (VSS), D67.3 (VSS), D68.3 (VSS), D69.3 (VSS), D70.3 (VSS), D71.3 (VSS), D72.3 (VSS), D75.3 (VSS), J3.1, J3.5, J4.1, J4.5; also elsewhere on the board

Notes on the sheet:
LED-Feld: 36 Kammern in der Reihenfolge der Datenkette (alle Platinen)
Kammer x,y = Spalte,Zeile auf der Master-Platine · D1…D75: SK6812RGBW · C101…C175: 100 nF am +5V-Pin der LED LED A wird immer bestückt, LED B wahlweise · JPn schließen, wenn LED B fehlt
Kammer 0,5 (#1)
Kammer 1,5 (#2)
Kammer 2,5 (#3)
Kammer 3,5 (#4)
Kammer 4,5 (#5)
Kammer 5,5 (#6)
Kammer 5,4 (#7)
Kammer 4,4 (#8)
Kammer 3,4 (#9)
Kammer 2,4 (#10)
Kammer 1,4 (#11)
Kammer 0,4 (#12)
Kammer 0,3 (#13)
Kammer 1,3 (#14)
Kammer 2,3 (#15)
Kammer 3,3 (#16)
Kammer 4,3 (#17)
Kammer 5,3 (#18)
Kammer 5,2 (#19)
Kammer 4,2 (#20)
Kammer 3,2 (#21)
Kammer 2,2 (#22)
Kammer 1,2 (#23)
Kammer 0,2 (#24)
Kammer 0,1 (#25)
Kammer 0,0 (#26)
Kammer 1,0 (#27)
Kammer 1,1 (#28)
Kammer 2,1 (#29)
Kammer 2,0 (#30)
Kammer 3,0 (#31)
Kammer 3,1 (#32)
Kammer 4,1 (#33)
Kammer 4,0 (#34)
Kammer 5,0 (#35)
Kammer 5,1 (#36)
Minutenpunkt
Kantenbrücken zur Nachbarplatine (0R 2512, von Hand)

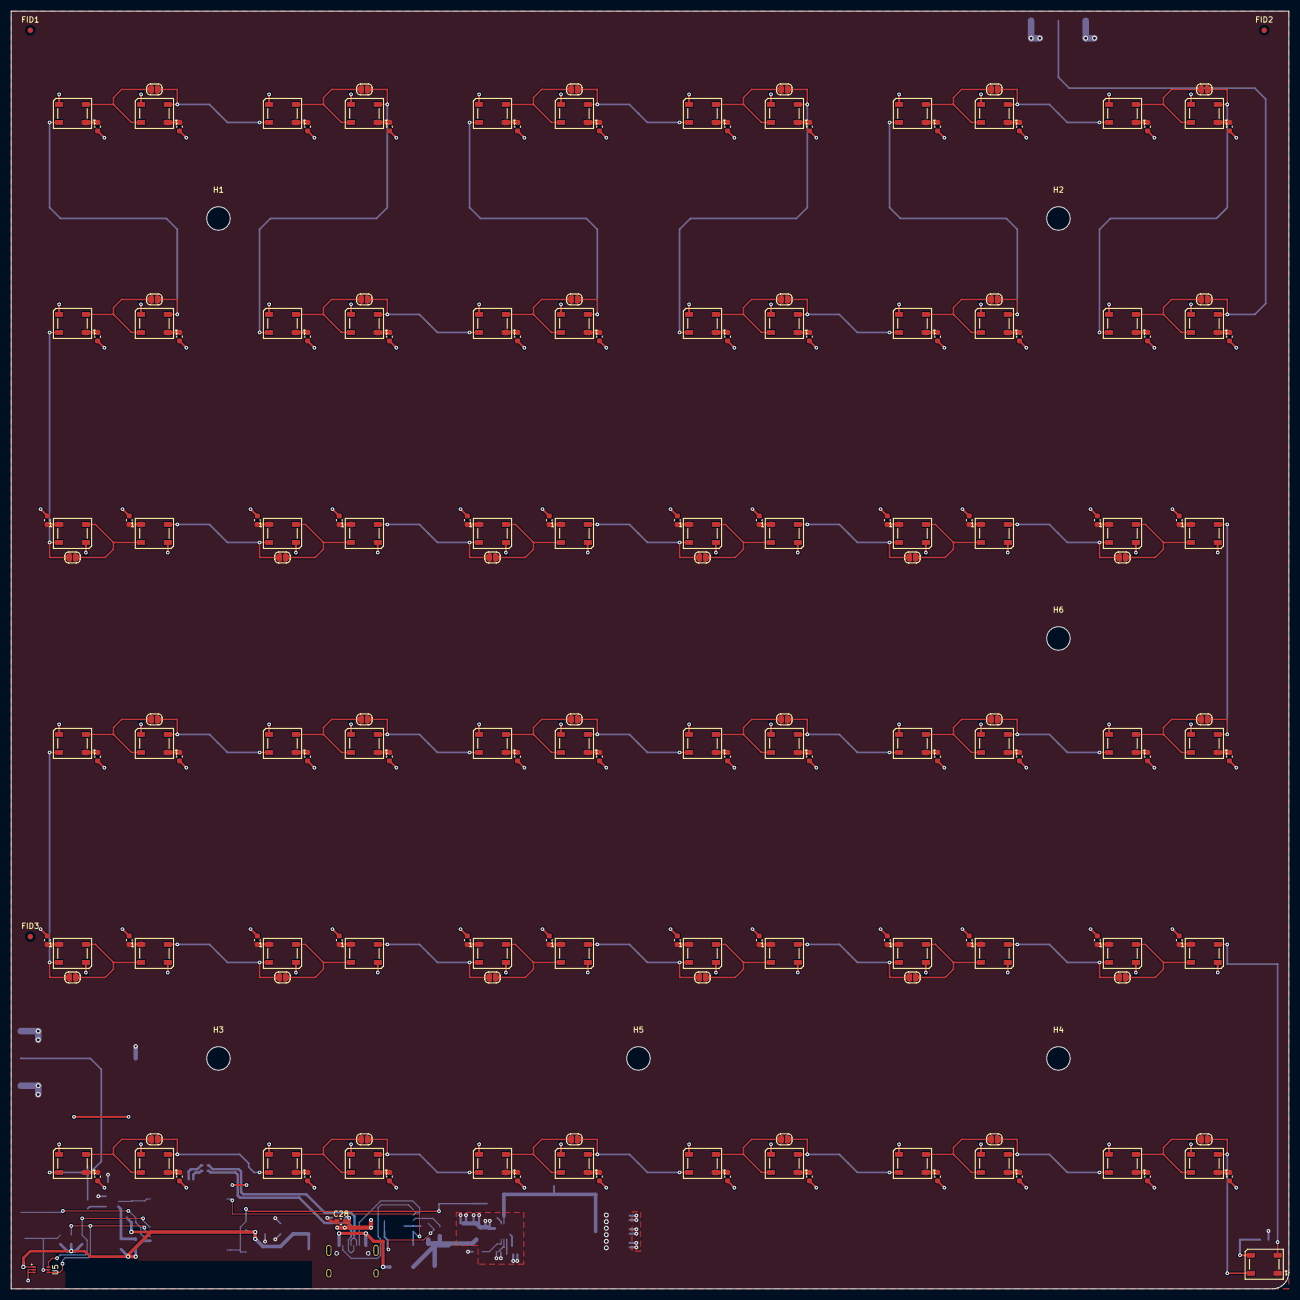
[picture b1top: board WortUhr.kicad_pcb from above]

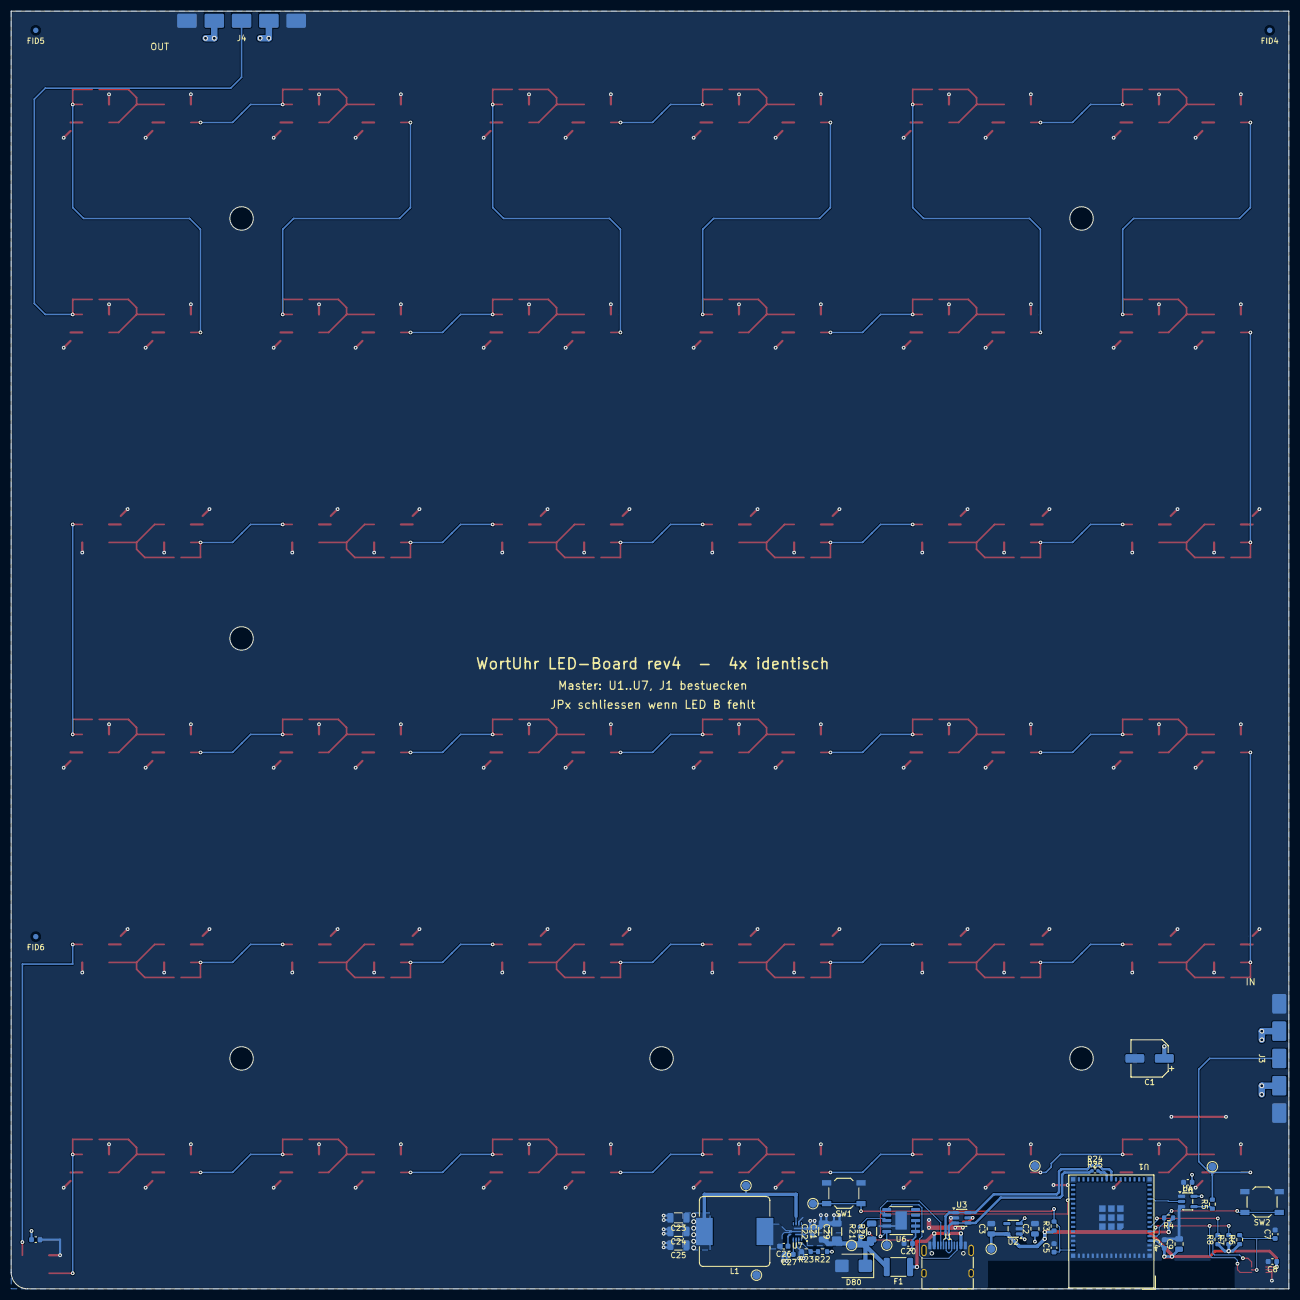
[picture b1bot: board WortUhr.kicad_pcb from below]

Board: 2 copper layers, 234.0 x 234.0 mm, 248 parts (56 on the bottom side), 99 nets.
